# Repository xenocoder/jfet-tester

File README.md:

JFET tester to match JFET values

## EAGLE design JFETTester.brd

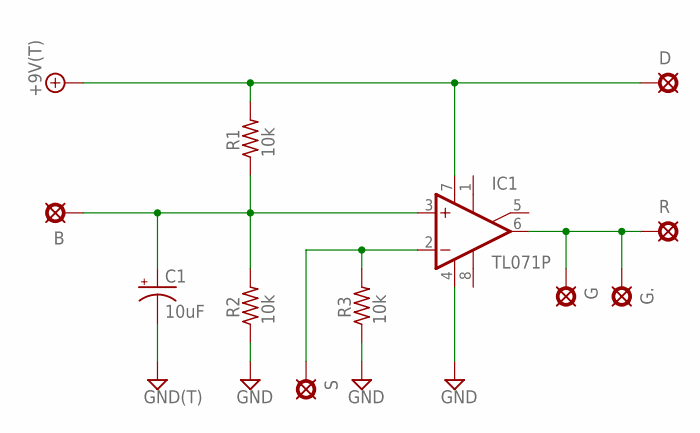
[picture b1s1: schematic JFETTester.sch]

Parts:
+9V: +9V(T); SQUARE
B: PAD; SQUARE
C1: 10uF; 050_020_1
D: PAD; SQUARE
G, G.: PAD; SQUARE
GND: GND(T); SQUARE
IC1: TL071P; DIL08
R: PAD; SQUARE
R1, R2, R3: 10k; R0207/1V
S: PAD; SQUARE

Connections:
+9V: +9V.1, D.1, IC1.7 (V+), R1.2
GND: C1.-, GND.1, IC1.4 (V-), R2.1, R3.1
unnamed: B.1, C1.+, IC1.3 (+IN), R1.1, R2.2
unnamed: IC1.2 (-IN), R3.2, S.1
unnamed: G.1, G..1, IC1.6 (OUT), R.1

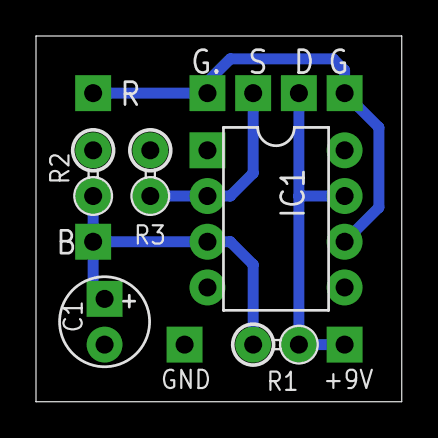
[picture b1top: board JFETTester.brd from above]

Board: 2 copper layers, 20.3 x 20.3 mm, 13 parts (0 on the bottom side), 5 nets.

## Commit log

2015-10-08 initial upload
